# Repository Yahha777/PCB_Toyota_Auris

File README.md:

# PCB_Toyota_Auris
Scheme and PCB for inverter Toyota Auris 3 in KiCAD format
This is my first time using CAD - I understand that a lot of things are done amateurishly.
PCB assembled, partially tested on 03.12.22. But this version has changes regarding UART ESP-32
The main difference from other Open inverter projects based on Toyota Prius and Auris for dual-motor boards is the use of the WiFi ESP-32 module.
In the /sd-card_adapter_esp32 directory, the diagram and PCB of the connector of the ESP module and micro SD card. (This has not been verified) Forum thread: https://openinverter.org/forum/viewtopic.php?t=2690

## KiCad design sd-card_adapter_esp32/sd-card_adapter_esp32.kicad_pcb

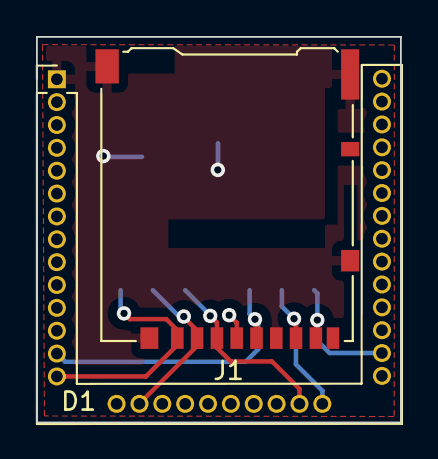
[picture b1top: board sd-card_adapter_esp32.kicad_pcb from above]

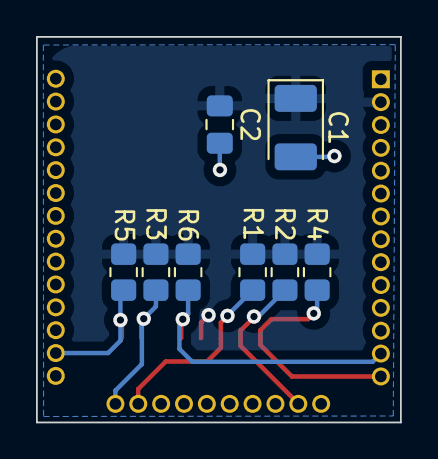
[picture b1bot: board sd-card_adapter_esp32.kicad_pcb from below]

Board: 2 copper layers, 20.2 x 21.4 mm, 10 parts (8 on the bottom side), 8 nets.

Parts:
C1: 100uF 6.3v; CP_EIA-3528-12_Kemet-T_Pad1.50x2.35mm_HandSolder
C2: 0.1uF; C_0805_2012Metric_Pad1.18x1.45mm_HandSolder
D1: esp32_adapter; adapter_esp32_for_sdcard
J1: Micro_SD_Card_Det_Hirose_DM3AT; microSD_HC_Hirose_DM3AT-SF-PEJM5
R1, R2, R3, R4, R5, R6: 3.3k; R_0805_2012Metric_Pad1.20x1.40mm_HandSolder

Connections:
+3.3V: C1.1, C2.1, D1.2 (3.3V), J1.4 (VDD), R1.2, R2.2, R3.2, R4.2, R5.2, R6.2
CLK_GPIO_14: D1.13 (GPIO_14), J1.5 (CLK), R6.1
CMD_GPIO_15: D1.23 (GPIO_15), J1.3 (CMD), R1.1
D0_GPIO_2: D1.24 (GPIO_2), J1.7 (DAT0), R3.1
D1_GPIO_4: D1.26 (GPIO_4), J1.8 (DAT1), R5.1
D2_GPIO_12: D1.14 (GPIO_12), J1.1 (DAT2), R4.1
D3_GPIO_13: D1.16 (GPIO_13), J1.2 (DAT3/CD), R2.1
GND: C1.2, C2.2, D1.1 (GND), J1.6 (VSS), J1.11 (SHIELD)
